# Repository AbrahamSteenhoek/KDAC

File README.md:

# KDAC
Keychain-sized DAC based on [Erik Soosalu's GrubDAC](http://www.diyforums.org/GrubDAC/GrubDACoverview.php)

The schematic is taken almost entirely from Soosalu's design, but the PCB layout has been modified to fit a smaller "key-chain sized" form factor.

Uses a USB-C connector instead of USB-mini B

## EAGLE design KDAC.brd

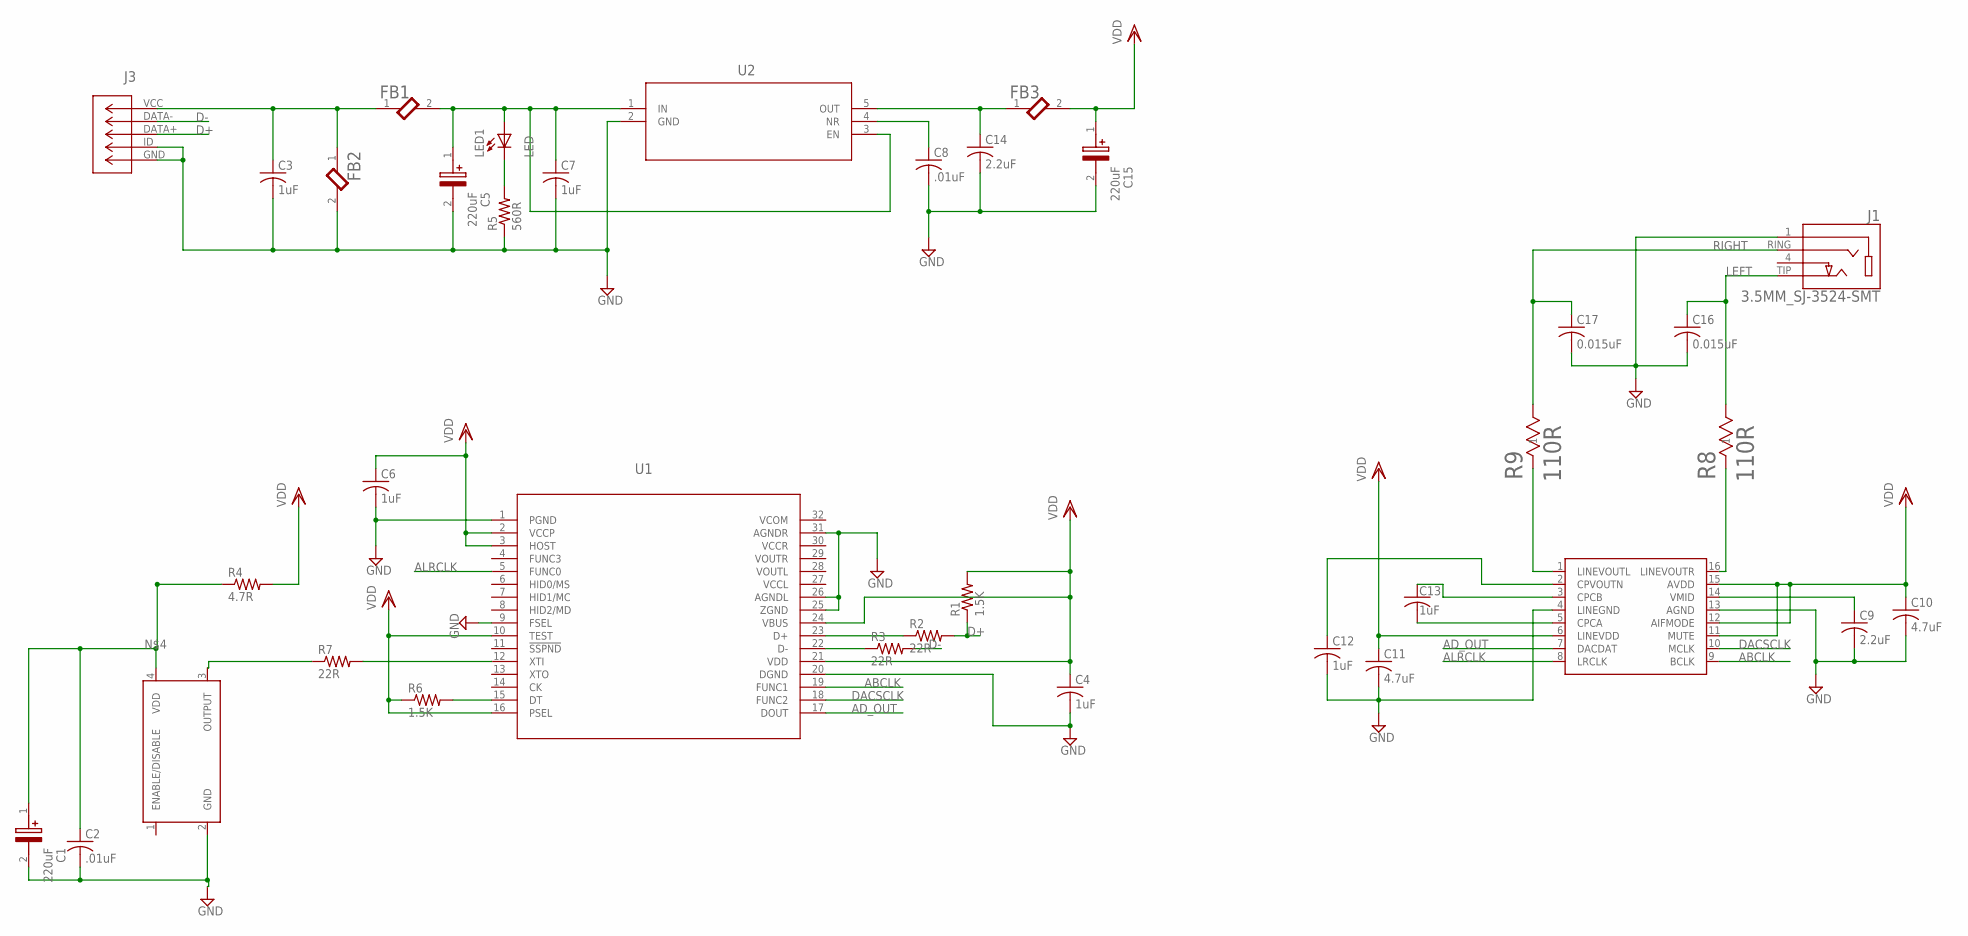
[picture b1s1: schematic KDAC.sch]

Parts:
C1, C5, C15: 220uF; CAPAE830X1050N
C2, C8: .01uF; C0805
C3, C4, C6, C7, C12, C13: 1uF; C0805
C9, C14: 2.2uF; C0805
C10, C11: 4.7uF; C0805
C16, C17: 0.015uF; C050-075X075
FB1, FB2, FB3: L_MURATA_BLM31PG601SN1LMURATA_BLM31PG601SN1L_0_2; MURATA_BLM31PG601SN1L_2
J1: 3.5MM_SJ-3524-SMT; CUI_SJ-3524-SMT
J3: USB-MICRO-B_10118192-0002LF; CONN_10118192-0002LF_AMP
LED1: LED; LED_2.54MM_0.5MM
R1, R6: 1.5K; R1206
R2, R3, R7: 22R; R1206
R4: 4.7R; R1206
R5: 560R; R1206
R8, R9: 110R; RES_CMF50
U1: PCM2706CPJTRPJT32-M; PJT32-M
U2: TPS79333DBVRDBV5_TEX-M; DBV5_TEX-M
U3: WM8524ALT; SOP65P640X110-16N
X1: ASV-12MHZ; ASV_12MHZ_4SMD-M

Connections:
ABCLK: U1.19 (FUNC1), U3.9 (BCLK)
AD_OUT: U1.17 (DOUT), U3.7 (DACDAT)
ALRCLK: U1.5 (FUNC0), U3.8 (LRCLK)
D+: J3.DATA+, R1.1, R2.2
D-: J3.DATA-, R3.2
DACSCLK: U1.18 (FUNC2), U3.10 (MCLK)
GND: C1.2 (-), C2.2, C3.2, C4.2, C5.2 (-), C6.2, C7.2, C8.2, C9.2, C10.2, C11.2, C12.2, C14.2, C15.2 (-), C16.2, C17.2, FB2.2, J1.1, J3.GND, J3.ID, R5.1, U1.1 (PGND), U1.9 (FSEL), U1.20 (DGND), U1.25 (ZGND), U1.26 (AGNDL), U1.31 (AGNDR), U2.2 (GND), U3.4 (LINEGND), U3.13 (AGND), X1.2 (GND)
LEFT: C16.1, J1.TIP (2), R8.2
unnamed: C3.1, FB1.1, FB2.1, J3.VCC
unnamed: C14.1, FB3.1, U2.5 (OUT)
unnamed: C5.1 (+), C7.1, FB1.2, LED1.ANODE (+), U2.1 (IN), U2.3 (EN)
unnamed: C1.1 (+), C2.1, R4.1, X1.4 (VDD)
unnamed: R7.2, U1.12 (XTI)
unnamed: R7.1, X1.3 (OUTPUT)
unnamed: LED1.CATHODE (-), R5.2
unnamed: C8.1, U2.4 (NR)
unnamed: R6.2, U1.15 (DT)
unnamed: R3.1, U1.22 (D-)
unnamed: R2.1, U1.23 (D+)
unnamed: C13.1, U3.3 (CPCB)
unnamed: C12.1, U3.2 (CPVOUTN)
unnamed: C9.1, U3.14 (VMID)
unnamed: C13.2, U3.5 (CPCA)
unnamed: R9.1, U3.1 (LINEVOUTL)
unnamed: R8.1, U3.16 (LINEVOUTR)
RIGHT: C17.1, J1.RING (3), R9.2
VCCL: U1.27 (VCCL)
VCCR: U1.30 (VCCR)
VCOM: U1.32 (VCOM)
VDD: C4.1, C6.1, C10.1, C11.1, C15.1 (+), FB3.2, R1.2, R4.2, R6.1, U1.2 (VCCP), U1.3 (HOST), U1.10 (TEST), U1.16 (PSEL), U1.21 (VDD), U1.24 (VBUS), U3.6 (LINEVDD), U3.11 (MUTE), U3.12 (AIFMODE), U3.15 (AVDD)

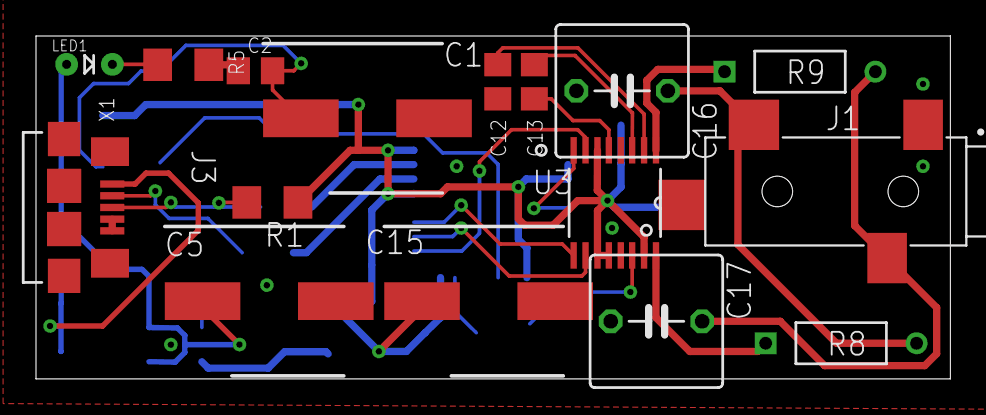
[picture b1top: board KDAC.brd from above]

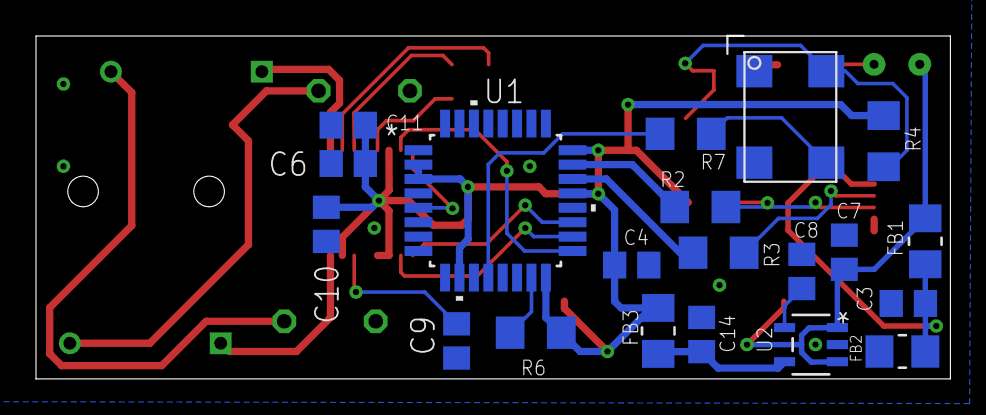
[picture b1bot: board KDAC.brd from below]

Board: 2 copper layers, 50.8 x 19.1 mm, 36 parts (20 on the bottom side), 27 nets.

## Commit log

2020-07-20 Update README.md
    Added a link to Soosalu's GrubDAC and description
2020-07-20 Bring files into GitHub
2020-07-31 Switch usb c to usb micro b
2020-08-02 Change

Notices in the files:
parts and their libraries:
COPYRIGHT: Copyright (C) 2018 Accelerated Designs. All rights reserved
